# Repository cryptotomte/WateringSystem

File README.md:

# WateringSystem v2.3 (Hardware-Managed LDO Architecture)

## Overview
Cost-effective automated plant watering system with **2-domain optical isolation** for practical greenhouse automation. Features ESP32-based control, RS485 Modbus soil sensors, and simplified safety design optimized for enclosed environments.

**🔥 Latest Update v2.3**: Upgraded to TXS0108E bidirectional level shifter for faster RS485 communication - 1800x faster signal propagation while maintaining cost-effectiveness and reliability.

## Table of Contents
- [Features](#features)
- [Hardware Requirements](#hardware-requirements)
- [Software Dependencies](#software-dependencies)
- [Installation](#installation)
- [Usage](#usage)
- [Documentation](#documentation)
- [Testing](#testing)
- [Safety](#safety)
- [Contributing](#contributing)
- [License](#license)

## 🌟 Key Features

### Practical Safety & Isolation
- **Fast Level Shifting**: TXS0108E provides rapid voltage translation (110 Mbps)
- **2-Domain Architecture**: ESP32 (3.3V) → FIELD Domain (5V, level shifted)
- **Cost Effective**: Ultra-low cost design with high performance
- **Greenhouse Optimized**: Practical design for enclosed 12V environments

### Professional Monitoring
- **Multi-Parameter Soil Analysis**: NPK, pH, EC, moisture, temperature via RS485 Modbus
- **Environmental Sensing**: BME280 for ambient temperature, humidity, pressure
- **Real-time Monitoring**: Web interface with live sensor data
- **Remote Web Interface**: Responsive monitoring and configuration portal

### Smart Power Management
- **Hardware-Only Control**: LDO voltage converters provide always-on power management
- **Extended Runtime**: >48h operation on 20Ah LiFePO4 battery
- **Solar Ready**: MC4 connectors for future solar panel integration
- **Battery Monitoring**: Real-time voltage and capacity tracking
- **Simplified Design**: No software power control eliminates failure points
- **Instant Operation**: Always-on design eliminates startup delays

## 🔧 Hardware Architecture

### Hardware-Managed LDO System
```
12V LiFePO4 BATTERY ──┬── AMS1117-3.3 LDO ──► ESP32 Control Domain (Always-On)
                      │                      │ TXS0108E Level Shifter (3.3V↔5V)
                      │                      └── FIELD Domain (RS485 + Sensors)
                      │
                      └── AMS1117-5.0 LDO ──► Field Power Supply (Always-On)
                               │
                               └── Common Ground (GND_COMMON)
```

### Core Components
| Component | Model | Function | Domain |
|-----------|-------|----------|---------|
| Microcontroller | ESP32-WROOM-32E | Main processor + WiFi | 3.3V Always-On |
| RS485 Interface | **SP3485EN** | Modbus communication | 5V Always-On |
| Level Shifter | **TXS0108E** | 3.3V↔5V voltage translation | Signal Path |
| Power Regulation | **AMS1117** | LDO voltage regulators | Hardware Control |
| Environmental | BME280 | Temperature/humidity | 3.3V Control |
| Soil Sensor | RS485 Modbus | NPK/pH/EC/moisture | 5V Field |

### ⚡ Hardware-Managed Safety Features
**LDO-based design provides reliable, always-on operation:**
- **Fast Level Shifting**: TXS0108E (110 Mbps capability with 10ns propagation)
- **Hardware Control**: LDO regulators eliminate software power management
- **Common Ground**: Simplified design prevents ground loop issues
- **Always-On**: Eliminates startup delays and power sequencing complexity
- **Maintenance Free**: No complex power domain monitoring required

## Software Dependencies
- **Framework**: Arduino framework for ESP32
- **Build System**: PlatformIO
- **Libraries**:
  - Wire (for I2C communication)
  - Adafruit BME280 (for environmental sensor)
  - ModbusMaster (for RS485 soil sensor)
  - ESPAsyncWebServer (for web interface)
  - AsyncElegantOTA (for OTA updates)
  - LittleFS (for file storage)
  - ArduinoJson (for data processing)

## Installation
1. Clone the repository:
```bash
git clone https://github.com/cryptotomte/WateringSystem.git
cd WateringSystem
```

2. Install PlatformIO (if not already installed):
```bash
pip install platformio
```

### Windows PowerShell Commands
On Windows systems, PlatformIO may not be in PATH. Use these commands:

```powershell
# Build project
& "C:\Users\crypt\.platformio\penv\Scripts\pio.exe" run --environment wateringsystem

# Upload to device  
& "C:\Users\crypt\.platformio\penv\Scripts\pio.exe" run --target upload --environment wateringsystem
```

3. Build and upload the firmware:
```bash
platformio run --target upload
```

4. Upload the file system (for web interface):
```bash
platformio run --target uploadfs
```

## Usage
1. **Initial Setup**
   - Power on the device
   - Connect to the WiFi network "WateringSystem-XXXX"
   - Navigate to 192.168.4.1 in your web browser
   - Follow the setup wizard to configure your home WiFi network

2. **Web Interface**
   - Access the web interface by navigating to the IP address of the device
   - Monitor current environmental and soil conditions
   - Configure watering schedules and thresholds
   - View historical data and system logs

3. **OTA Updates**
   - Access the update page at http://[device-ip]/update
   - Upload new firmware files through the web interface

## Documentation
Detailed documentation is available in the `docs` directory:
- [System Requirements Specification](docs/requirements.md)
- [Architecture Documentation](docs/architecture.md)
- [Hardware Documentation](docs/hardware.md)
- [User Guide](docs/user-guide.md)
- [Testing Documentation](docs/testing.md)
- [Safety Documentation](docs/safety.md)
- [Release Notes](docs/release-notes.md)

## Testing
The system includes unit tests and integration tests that can be executed using PlatformIO:

```bash
# Run all tests
platformio test

# Run specific test
platformio test -e test_sensors
```

For complete testing documentation, see [Testing Documentation](docs/testing.md).

## Safety
The WateringSystem interfaces with both water and electricity. Important safety considerations:
- All electrical components must be properly isolated from water
- Use waterproof enclosure for outdoor installations
- Include proper grounding for lightning protection in outdoor installations
- Power supply must be isolated and conform to safety standards

For complete safety information, see [Safety Documentation](docs/safety.md).

## Contributing
Contributions to the WateringSystem project are welcome! Please read [CONTRIBUTING.md](CONTRIBUTING.md) for details on our code of conduct and the process for submitting pull requests.

## License
This project is licensed under the GNU Affero General Public License v3.0 or later (AGPL-3.0-or-later) - see the [LICENSE](LICENSE) file for details.

**Key License Points:**
- ✅ Commercial use allowed
- ✅ Private use allowed  
- ✅ Modification allowed
- ⚠️ **Must share source code** when distributing binaries
- ⚠️ **Must share source code** when running as network service (SaaS)
- ⚠️ **Must preserve copyright** and license notices
- ⚠️ All modifications must use the same license

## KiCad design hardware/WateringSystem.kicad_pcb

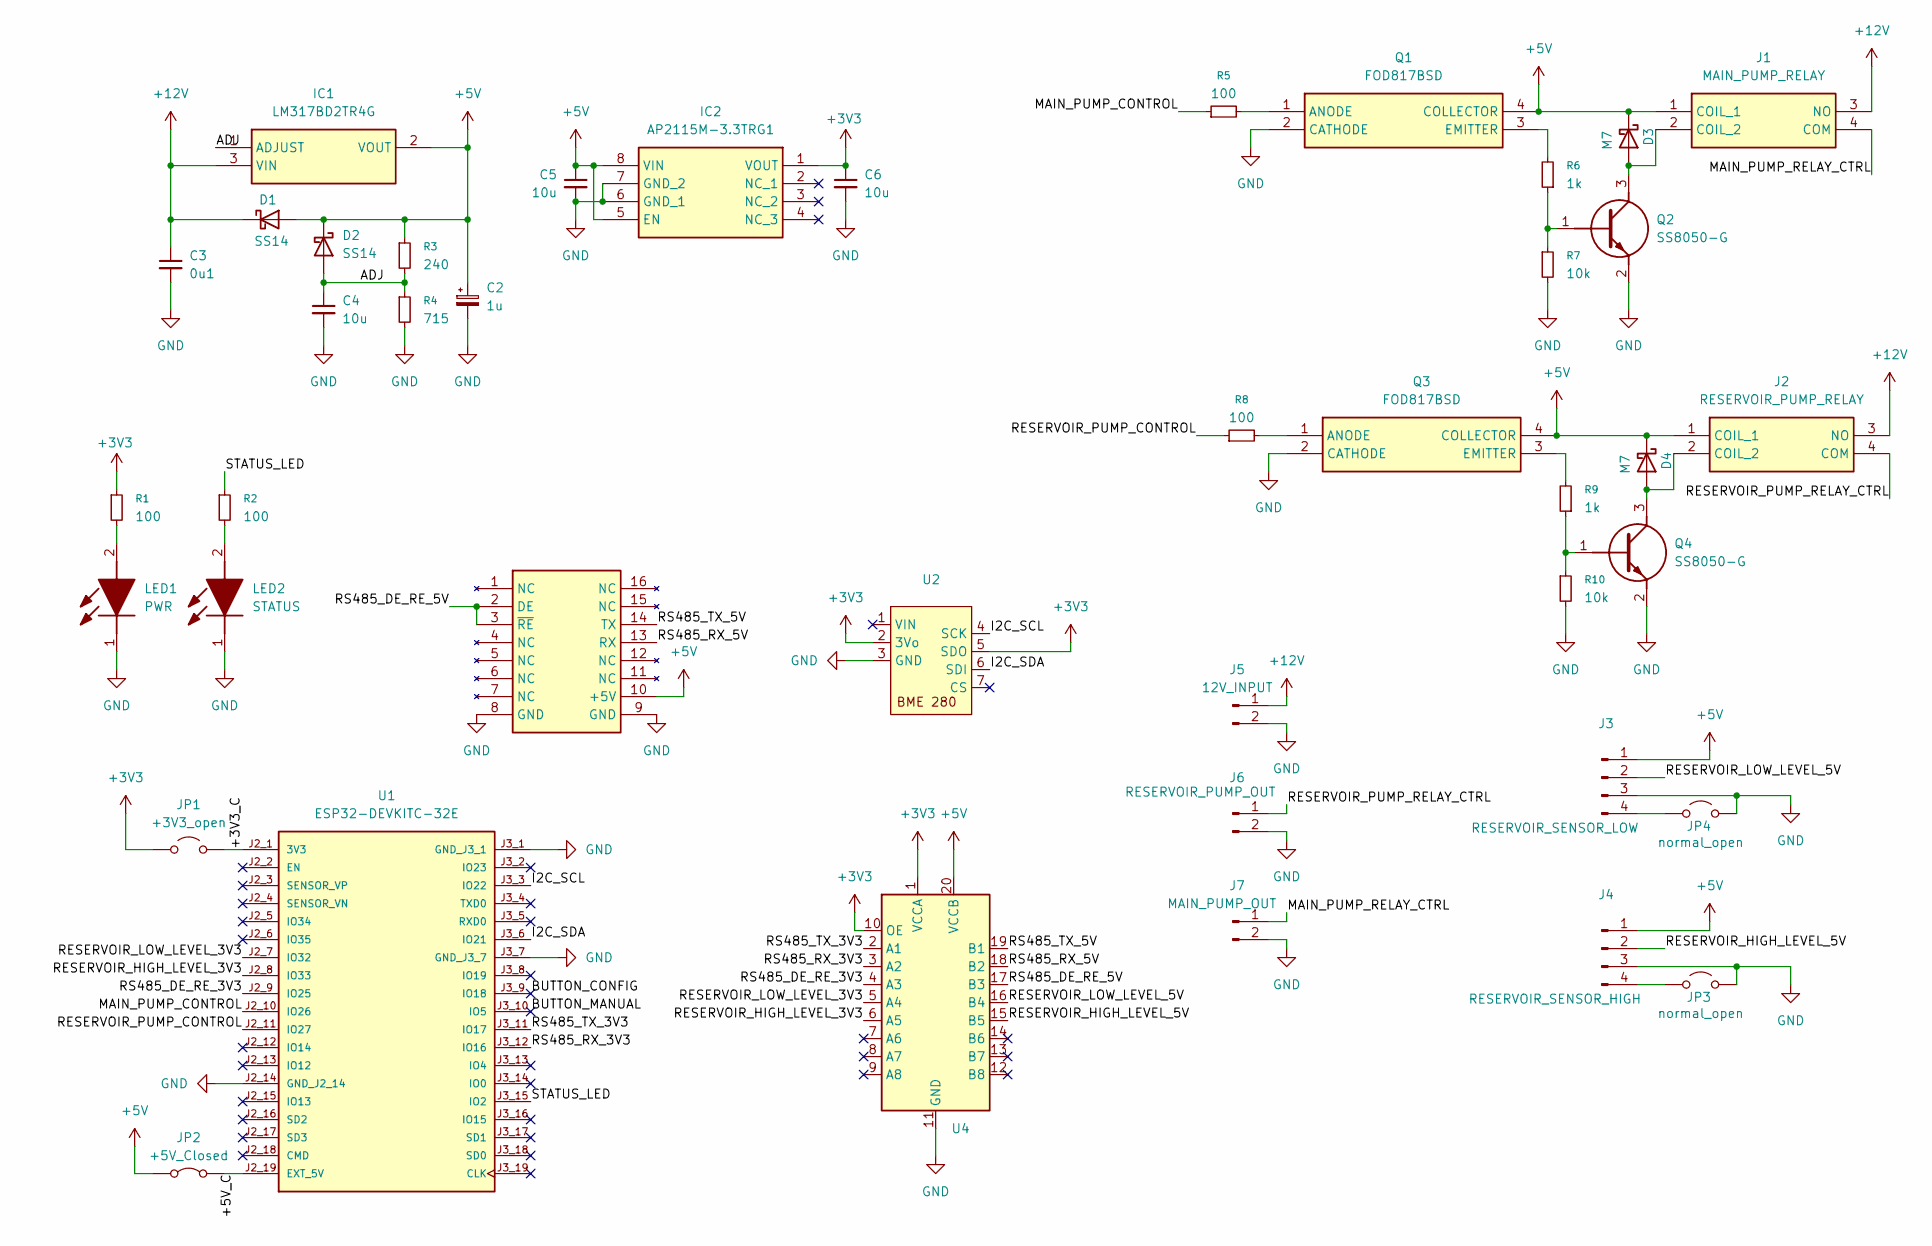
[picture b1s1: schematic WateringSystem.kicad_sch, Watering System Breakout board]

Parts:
Breakoutboard1: MAX485ESA+T_breakout
C2: 1u; CP_EIA-2012-12_Kemet-R
C3: 0u1; C_0805_2012Metric
C4, C5, C6: 10u; C_0805_2012Metric
D1, D2: SS14; D_SMA
D3, D4: M7; D_SMA
IC1: LM317BD2TR4G; Mouser Part Number 863-LM317BD2TR4G
IC2: AP2115M-3.3TRG1; SOIC127P600X175-8N; Mouser Part Number 621-AP2115M-3.3TRG1
J1: MAIN_PUMP_RELAY; 120715561; Mouser Part Number 655-1-2071556-1
J2: RESERVOIR_PUMP_RELAY; 120715561; Mouser Part Number 655-1-2071556-1
J3: RESERVOIR_SENSOR_LOW; JST_XH_B4B-XH-A_1x04_P2.50mm_Vertical
J4: RESERVOIR_SENSOR_HIGH; JST_XH_B4B-XH-A_1x04_P2.50mm_Vertical
J5: 12V_INPUT; WEID_1715010000
J6: RESERVOIR_PUMP_OUT; WEID_1715010000
J7: MAIN_PUMP_OUT; WEID_1715010000
JP1: +3V3_open; SolderJumper-2_P1.3mm_Open_RoundedPad1.0x1.5mm
JP2: +5V_Closed; SolderJumper-2_P1.3mm_Bridged_RoundedPad1.0x1.5mm
JP3, JP4: normal_open; SolderJumper-2_P1.3mm_Open_RoundedPad1.0x1.5mm
LED1: PWR; 150080SS75000; Mouser Part Number 710-150080SS75000
LED2: STATUS; LEDC2012X80N; Mouser Part Number 710-150080VS75000
Q1, Q3: FOD817BSD; SOP254P1016X385-4N; Mouser Part Number 512-FOD817BSD
Q2, Q4: SS8050-G; SOT95P240X115-3N; Mouser Part Number 750-SS8050-G
R1, R2, R5, R8: 100; R_0805_2012Metric
R3: 240; R_0805_2012Metric
R4: 715; R_0805_2012Metric
R6, R9: 1k; R_0805_2012Metric
R7, R10: 10k; R_0805_2012Metric
U1: ESP32-DEVKITC-32E; ESP32-DEVKITC-32E_MODULE_ESP32-DEVKITC-32E-for headers; PARTREV 1.4; DigiKey_Part_Number 1965-ESP32-DEVKITC-32E-ND
U2: BME_280_qt_version
U4: TXS10108E_breakout

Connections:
+3V3: C6.1, IC2.1 (VOUT), JP1.1 (A), R1.1, U2.2 (3Vo), U2.5 (SDO), U4.1 (VCCA), U4.10 (OE)
+5V: Breakoutboard1.10 (+5V), C2.1, C5.1, D1.2 (A), D2.1 (K), D3.1 (K), D4.1 (K), IC1.2 (VOUT), IC2.5 (EN), IC2.8 (VIN), J1.1 (COIL_1), J2.1 (COIL_1), J3.1, J4.1, JP2.1 (A), Q1.4 (COLLECTOR), Q3.4 (COLLECTOR), R3.1, U4.20 (VCCB)
+12V: C3.1, D1.1 (K), IC1.3 (VIN), J1.3 (NO), J2.3 (NO), J5.1
/+3V3_C: JP1.2 (B), U1.J2_1 (3V3)
/+5V_C: JP2.2 (B), U1.J2_19 (EXT_5V)
/ADJ: C4.1, D2.2 (A), IC1.1 (ADJUST), R3.2, R4.1
/BUTTON_CONFIG: U1.J3_9 (IO18)
/BUTTON_MANUAL: U1.J3_10 (IO5)
/I2C_SCL: U1.J3_3 (IO22), U2.4 (SCK)
/I2C_SDA: U1.J3_6 (IO21), U2.6 (SDI)
/MAIN_PUMP_CONTROL: R5.1, U1.J2_10 (IO26)
/MAIN_PUMP_RELAY_CTRL: J1.4 (COM), J7.1
/RESERVOIR_HIGH_LEVEL_3V3: U1.J2_8 (IO33), U4.6 (A5)
/RESERVOIR_HIGH_LEVEL_5V: J4.2, U4.15 (B5)
/RESERVOIR_LOW_LEVEL_3V3: U1.J2_7 (IO32), U4.5 (A4)
/RESERVOIR_LOW_LEVEL_5V: J3.2, U4.16 (B4)
/RESERVOIR_PUMP_CONTROL: R8.1, U1.J2_11 (IO27)
/RESERVOIR_PUMP_RELAY_CTRL: J2.4 (COM), J6.1
/RS485_DE_RE_3V3: U1.J2_9 (IO25), U4.4 (A3)
/RS485_DE_RE_5V: Breakoutboard1.2 (DE), Breakoutboard1.3 (~RE), U4.17 (B3)
/RS485_RX_3V3: U1.J3_12 (IO16), U4.3 (A2)
/RS485_RX_5V: Breakoutboard1.13 (RX), U4.18 (B2)
/RS485_TX_3V3: U1.J3_11 (IO17), U4.2 (A1)
/RS485_TX_5V: Breakoutboard1.14 (TX), U4.19 (B1)
/STATUS_LED: R2.1, U1.J3_15 (IO2)
GND: Breakoutboard1.8 (GND), Breakoutboard1.9 (GND), C2.2, C3.2, C4.2, C5.2, C6.2, IC2.6 (GND_1), IC2.7 (GND_2), J3.3, J4.3, J5.2, J6.2, J7.2, JP3.2 (B), JP4.2 (B), LED1.1 (K), LED2.1 (K), Q1.2 (CATHODE), Q2.2 (E), Q3.2 (CATHODE), Q4.2 (E), R4.2, R7.2, R10.2, U1.J2_14 (GND_J2_14), U1.J3_1 (GND_J3_1), U1.J3_7 (GND_J3_7), U2.3 (GND), U4.11 (GND)
unnamed: D3.2 (A), J1.2 (COIL_2), Q2.3 (C)
unnamed: D4.2 (A), J2.2 (COIL_2), Q4.3 (C)
unnamed: J3.4, JP4.1 (A)
unnamed: J4.4, JP3.1 (A)
unnamed: LED1.2 (A), R1.2
unnamed: LED2.2 (A), R2.2
unnamed: Q1.1 (ANODE), R5.2
unnamed: Q1.3 (EMITTER), R6.2
unnamed: Q2.1 (B), R6.1, R7.1
unnamed: Q3.1 (ANODE), R8.2
unnamed: Q3.3 (EMITTER), R9.2
unnamed: Q4.1 (B), R9.1, R10.1

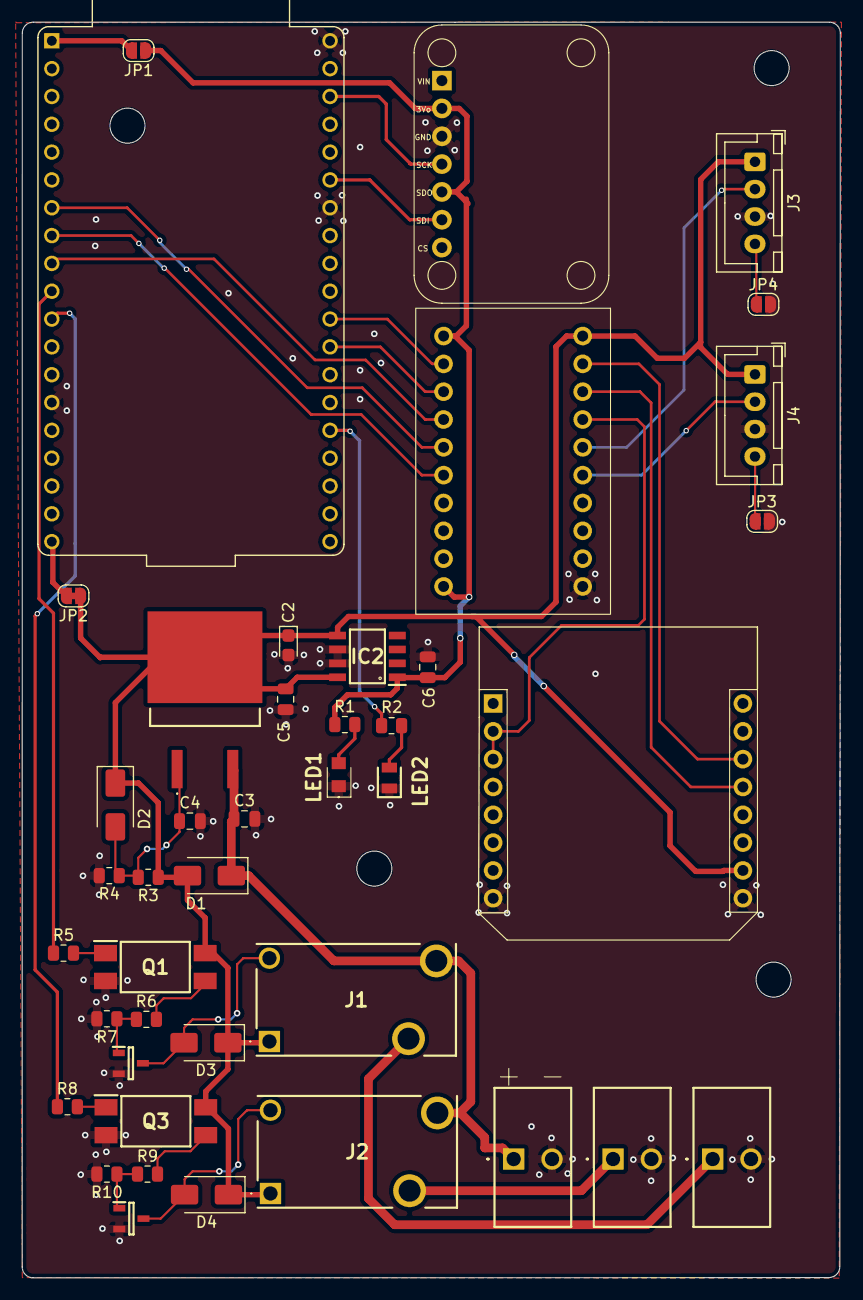
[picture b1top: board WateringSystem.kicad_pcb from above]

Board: 4 copper layers, 74.7 x 114.6 mm, 42 parts (0 on the bottom side), 36 nets.

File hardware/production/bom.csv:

Designator,Footprint,Quantity,Value,LCSC Part #
BREAKOUTBOARD1,MAX485ESA+T_breakout,1,~,
C2,CP_EIA-2012-12_Kemet-R,1,1u,
C3,0805,1,0u1,
"C4, C5, C6",0805,3,10u,
"D1, D2",D_SMA,2,SS14,
"D3, D4",D_SMA,2,M7,
IC1,LM317BD2TR4G,1,LM317BD2TR4G,
IC2,SOIC127P600X175-8N,1,AP2115M-3.3TRG1,
J1,120715561,1,MAIN_PUMP_RELAY,
J2,120715561,1,RESERVOIR_PUMP_RELAY,
J3,JST_XH_B4B-XH-A_1x04_P2.50mm_Vertical,1,RESERVOIR_SENSOR_LOW,
J4,JST_XH_B4B-XH-A_1x04_P2.50mm_Vertical,1,RESERVOIR_SENSOR_HIGH,
J5,WEID_1715010000,1,12V_INPUT,
J6,WEID_1715010000,1,RESERVOIR_PUMP_OUT,
J7,WEID_1715010000,1,MAIN_PUMP_OUT,
JP1,SolderJumper-2_P1.3mm_Open_RoundedPad1.0x1.5mm,1,+3V3_open,
JP2,SolderJumper-2_P1.3mm_Bridged_RoundedPad1.0x1.5mm,1,+5V_Closed,
"JP3, JP4",SolderJumper-2_P1.3mm_Open_RoundedPad1.0x1.5mm,2,normal_open,
LED1,150080SS75000,1,PWR,
LED2,LEDC2012X80N,1,STATUS,
"Q1, Q3",SOP254P1016X385-4N,2,FOD817BSD,
"Q2, Q4",SOT95P240X115-3N,2,SS8050-G,
"R1, R2, R5, R8",0805,4,100,
"R10, R7",0805,2,10k,
R3,0805,1,240,
R4,0805,1,715,
"R6, R9",0805,2,1k,
U1,ESP32-DEVKITC-32E_MODULE_ESP32-DEVKITC-32E-for headers,1,ESP32-DEVKITC-32E,
U2,BME_280_qt_version,1,~,
U4,TXS10108E_breakout,1,~,

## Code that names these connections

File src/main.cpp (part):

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#include "hardware/RS485Config.h" // Hardware configuration for RS485

// Pin definitions based on hardware.md specification with TXS0108E level shifter
#define PIN_I2C_SDA           21
#define PIN_I2C_SCL           22
#define PIN_RS485_TX          16  // ESP32 TX -> TXS0108E A2 -> B2 -> Click pin13 (DI)
#define PIN_RS485_RX          17  // ESP32 RX <- TXS0108E A1 <- B1 <- Click pin14 (RO)
#define PIN_RS485_DE          25  // Direction control via TXS0108E A3
#define PIN_MAIN_PUMP_CONTROL 26  // Main Water Pump MOSFET Gate (unchanged)
#define PIN_RESERVOIR_PUMP_CONTROL 27  // Reservoir Filling Pump MOSFET Gate (unchanged)
#define PIN_RESERVOIR_LOW_LEVEL   32  // Sensor for low water level in reservoir (unchanged)
#define PIN_RESERVOIR_HIGH_LEVEL  33  // Sensor for high water level in reservoir (unchanged)
#define PIN_STATUS_LED        2       
#define PIN_BUTTON_MANUAL     5       
#define PIN_BUTTON_CONFIG     18

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HardwareSerial rs485Serial(2);  // Using UART2 for RS485
SP3485ModbusClient modbusClient(&rs485Serial, PIN_RS485_DE); // Using TXS0108E level shifter - hardware managed
ModbusSoilSensor soilSensor(&modbusClient, SOIL_SENSOR_MODBUS_ADDR, "SoilSensor");
WaterPump plantPump(PIN_MAIN_PUMP_CONTROL, "PlantPump");         // Renamed for clarity
WaterPump reservoirPump(PIN_RESERVOIR_PUMP_CONTROL, "ReservoirPump"); // Added new pump for filling reservoir
LittleFSStorage dataStorage;
WateringController controller(&envSensor, &soilSensor, &plantPump, &dataStorage);
WateringSystemWebServer webServer(&controller, &envSensor, &soilSensor, &plantPump, &dataStorage, WEB_SERVER_PORT, &reservoirPump);
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    while (WiFi.status() != WL_CONNECTED && 
           millis() - startAttemptTime < WIFI_TIMEOUT) {
        Serial.print(".");
        digitalWrite(PIN_STATUS_LED, !digitalRead(PIN_STATUS_LED));  // Toggle LED
        delay(500);
    }
    
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  Serial.println("Architecture: LDO-powered domains with TXS0108E level shifting");
  
  // Initialize status LED
  pinMode(PIN_STATUS_LED, OUTPUT);
  digitalWrite(PIN_STATUS_LED, HIGH);  // Turn on while initializing
  
  // Initialize buttons with pull-ups
  pinMode(PIN_BUTTON_MANUAL, INPUT_PULLUP);
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  pinMode(PIN_RESERVOIR_LOW_LEVEL, INPUT_PULLUP);
  pinMode(PIN_RESERVOIR_HIGH_LEVEL, INPUT_PULLUP);
    // Initialize I2C for BME280 (ESP32 domain)
  Wire.begin(PIN_I2C_SDA, PIN_I2C_SCL);
  Serial.println("I2C initialized for BME280");
    // Initialize RS485 UART with TXS0108E level shifter
  rs485Serial.begin(9600, SERIAL_8N1, PIN_RS485_RX, PIN_RS485_TX);
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  systemReady = true;
  
  // Turn off status LED once system is ready
  digitalWrite(PIN_STATUS_LED, LOW);
  
  Serial.println("System initialization complete");
  Serial.println("--------------------------------------------");
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  // LED status indication
  if (apMode) {
    // Fast blinking in AP mode
    digitalWrite(PIN_STATUS_LED, ((millis() / 200) % 2) ? HIGH : LOW);
  } else if (plantPump.isRunning()) {
    // Medium blinking when pump is running
    digitalWrite(PIN_STATUS_LED, ((millis() / 500) % 2) ? HIGH : LOW);
  } else {
    // Just a short blink every 3 seconds to show system is running
    digitalWrite(PIN_STATUS_LED, ((millis() % 3000) < 100) ? HIGH : LOW);  }
    // Monitor and maintain WiFi connection
  monitorWiFiConnection();
  
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    while (digitalRead(PIN_BUTTON_CONFIG) == LOW && configButtonHoldTime < 50) {
        delay(100);
        configButtonHoldTime++;
        digitalWrite(PIN_STATUS_LED, configButtonHoldTime % 2);  // Blink LED
    }
    
    if (configButtonHoldTime >= 50) {  // Button held for 5+ seconds
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
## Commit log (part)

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2025-04-15 Inital project setup
2025-04-15 Add AsyncElegantOTA support and web interface files
2025-04-15 Update README.md with comprehensive project description and features
2025-04-15 Uppdaterat författarnamn i alla header- och implementationsfiler
2025-04-15 Add update method to IWaterPump interface
2025-04-15 Rename WebServer to WateringSystemWebServer to avoid conflicts
    - Renamed class and files to WateringSystemWebServer to avoid name conflicts with ESP32's built-in WebServer
    - Created new header and implementation files with the new name
    - Updated main.cpp to use the new header file
    - Maintained the same functionality without behavioral changes
    - Removed old WebServer files
2025-04-15 Update header files with consistent include guards and formatting
    - Update all header files with consistent include guards
    - Fix formatting and comments in header files
    - Add wifi_setup.html for AP mode configuration
    - Update platformio.ini build settings
2025-04-16 Add reservoir pump control and improve system management
    - Add reservoir pump on pin 27 for filling the water reservoir
    - Move status LED to pin 2 (was previously on pin 27)
    - Rename waterPump to plantPump for better clarity
    - Update pin definitions for improved readability
    - Add WebServer implementation files
    - Update documentation in user-guide
2025-04-16 Add reservoir pump functionality with auto-fill feature
    - Add new hardware support for reservoir pump and water level sensors
    - Implement reservoir control logic in main.cpp
    - Update web interface with reservoir management controls
    - Update documentation with reservoir pump specifications
    - Fix getReservoirStatus function to return bool according to callback type
    - Fix method name in ModbusSoilSensor from writeHoldingRegister to writeSingleRegister
2025-04-16 Fix auto watering toggle functionality in web interface
    - Implement AsyncCallbackJsonWebHandler for proper JSON parsing
    - Separate handlers for JSON and form-based requests
    - Improve debug logging for better troubleshooting
    - Update header file with new method declarations
    The web interface can now correctly enable/disable auto watering through
    the JSON API endpoints.
2025-04-17 fix: Remove empty :root rule in styles.css
2025-04-17 refactor: update main.cpp and remove deprecated WebServer.cpp
2025-05-05 Fix LittleFS file path handling and config file management
    - Update LittleFSStorage to properly handle file paths with leading slashes
    - Add automatic creation of config.json file when missing
    - Improve error handling and logging for file operations
    - Fix endpoint path handling in WateringSystemWebServer class
    - Update LittleFSStorage constructor to handle String objects correctly
    - Add detailed logging for debugging file path issues
2025-05-05 fix: use form data instead of JSON for watering requests
    - Change startWatering function to use form data format
    - Remove problematic raw body handler in WateringSystemWebServer
    - Add favicon references to HTML files
    - Fix memory leak issues with AsyncWebServer JSON handling
    The ESP32's AsyncWebServer library has issues with JSON data on
    /control/water/start endpoint, causing memory leaks and device crashes
2025-05-05 add: include favicon and update header files
    - Add favicon.ico for web interface
    - Update WateringSystemWebServer.h with proper function declarations
    - Improve debug logging in WaterPump.cpp for better troubleshooting
    - Complete the fix for the JSON handling issue
2025-05-06 chore: remove launch.json exception from .gitignore
    - Exclude VS Code launch.json from version control
    - Add comment explaining why launch.json should be ignored
    - This prevents user-specific configurations from being committed
2025-05-28 feat: Implement dark theme and improve reservoir control layout
2025-06-03 style: update wifi_setup.html to match modern Tailwind CSS design
2025-06-09 Simplify architecture to cost-effective 2-domain system
    - Replace complex 3-domain isolation with practical 2-domain optical isolation
    - Remove expensive MIKROE-4156 and TMR 1-1215 components
    - Update BOM cost from ~6000 SEK to 3108 SEK (50% reduction)
    - Clean up 18 duplicate/outdated documentation files
    - Update all documentation for simplified FOD817BSD-only isolation
    - Maintain 5kV optical isolation adequate for greenhouse environments
2025-06-09 Add documentation cleanup completion report - Comprehensive summary of architecture simplification - Cost analysis showing 50% BOM reduction - Technical validation of 2-domain optical isolation - Com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
2025-06-09 Update gitignore to exclude local PlatformIO documentation
2025-06-09 Remove auto-generated documentation files and enhance WiFi stability
    - Remove outdated documentation files that were auto-restored by VS Code
    - Keep only essential docs: requirements.md, architecture.md, hardware.md
    - Enhanced WiFi stability with monitoring, diagnostics, and auto-reconnection
    - Added software watchdog and emergency WiFi reset functionality
    - Improved web interface connection status handling
2025-06-09 Update gitignore to prevent auto-generated files
2025-06-09 Add documentation backup file explaining auto-restore issue
2025-06-10 Fix critical sensor failure and implement emergency safety measures
    - Add brownout detector disable to prevent WiFi-related resets
    - Implement comprehensive fail-safe mechanisms for sensor timeouts
    - Add timestamp-based sensor validation with 30-second timeout
    - Emergency pump stop when sensor data unavailable
    - Enhanced debug infrastructure for sensor initialization
    - Improve RS485 communication timing and error handling
2025-06-11 Upgrade from FOD817 optocouplers to TXS0108E level shifter
    - Replace FOD817BSD optical isolation with TXS0108E bidirectional level shifter
    - Achieve 1800x faster signal propagation (10ns vs 18µs)
    - Support up to 110 Mbps data rate vs ~1 Mbps limitation
    - Reduce component count from 3 optocouplers to 1 level shifter IC
    - Update timing constants for faster DE/RE switching (10µs vs 200µs)
    - Modify GPIO pin assignments for TXS0108E Output Enable (GPIO 26)
2025-06-11 Remove temporary documentation and improve web UI responsiveness
    - Remove KORREKT_KOMPONENTBYTE.md (changes documented in commit history)
    - Update web UI refresh rate: system status now updates every 5 seconds
    - Water level indicator and pump status now respond much faster
    - Improves user experience for reservoir pump monitoring
    Performance improvements:
    - Water level updates: 15s 5s (3x faster)
2025-06-16 Add initial KiCad 9 project files for PCB design
    - Add WateringSystem.kicad_pro: Project configuration file
    - Add WateringSystem.kicad_sch: Empty schematic ready for component placement
    - Add WateringSystem.kicad_pcb: Empty PCB layout ready for routing
    - Add sym-lib-table: Symbol library configuration table
    Project structure now ready for:
    - ESP32 and sensor component placement
2025-06-25 Fix gitignore pattern for KiCad autosave files
    - Add ~_autosave* pattern to properly ignore files starting with tilde
    - Ensures lock files like ~_autosave-*.kicad_pcb.lck are properly ignored
2025-07-05 Fix manual watering mode and remove soil sensor debug logging
    - Add manual mode support to WaterPump with isManualMode() and setManualMode()
    - Modify safety functions to only apply to automatic watering mode
    - Manual watering now bypasses sensor-based safety checks
    - Remove excessive DEBUG-INIT logging from soil sensor initialization
    - Fix timing display bug in pump debug messages
    - Add comprehensive debug logging for pump operations with mode tracking
2025-07-24 Fix RS485 communication and update documentation
    Major improvements to RS485 Modbus soil sensor communication:
    Hardware fixes:
    - Fix GPIO pin configuration: TX=GPIO17, RX=GPIO16 (was swapped)
    - Optimize TXS0108E timing delays from 10µs to 50µs for reliable switching
    - Update RS485Config.h with verified timing constants
    Software improvements:
2025-07-29 Add rs485test diagnostic command and fix soil sensor communication
    - Implement rs485test/test commands in handleSerialCommands()
    - Add isolated RS485 client testing functionality
    - Parse and display raw register values with detailed output
    - Enable runtime diagnostics for soil sensor troubleshooting
    - Successfully resolved Error 3 communication issues
    - Production system now fully functional with soil sensor readings
2025-08-22 Change license from MIT to AGPL-3.0-or-later
    - Replace LICENSE with full AGPL-3.0-or-later text
    - Add SPDX headers to all source files (.cpp, .h)
    - Update CONTRIBUTING.md with DCO and copyleft requirements
    - Preserve attribution and require source sharing for modifications
    - Ensure commercial use allowed but changes must be returned
2025-08-22 Update README.md license references from MIT to AGPL-3.0-or-later
    - Change license badge from MIT to AGPL-3.0-or-later
    - Update License section with detailed AGPL-3.0-or-later explanation
    - Add key license points highlighting copyleft requirements
    - Clarify source code sharing obligations for distribution and SaaS
2026-04-12 Lägg till feature-ideas.md med multi-zon och produktions-PCB koncept
2026-06-09 hardware: commit April design work — schematic pin fixes, PCB layout session, rev2 BOM (THVD1426), JLCPCB production files
2026-06-09 added needed changes to these files
2026-06-09 chore: initialize spec-kit
2026-06-11 docs(spec): PR-06 nvs-littlefs-storage spec, plan, tasks and design artifacts
    - Feature spec with 2026-06-11 clarifications (>=30-day retention,
    settable interval items, reservoir flags deferred to PR-05)
    - Plan with verified research D1-D10 (littlefs image build, NVS on
    linux target, atomicity model), data model, contracts, quickstart
    - 36 tasks across 8 phases; cross-artifact analysis findings fixed
    (FR-013 Locked* decorators, 10-metric budget cap, linux-target
2026-06-12 feat(interfaces): IDataStorage contract header
    Sensor history, rotating event log and storage statistics interface
    per contracts/IDataStorage.md. Contract-level bounds (kMaxMetrics,
    kEventDetailMaxLen, event categories) live here as the single source
    of truth for implementations, mocks and tests.
    Task: T015
    Spec: 003-nvs-littlefs-storage
2026-06-12 feat(storage): LittleFsDataStorage declaration and stub
    POSIX-stdio data storage skeleton with injectable base path and
    stats provider (no esp_littlefs/IDF includes, builds on the linux
    preview target). History methods stubbed for T021, event methods
    for T024. Registered in the storage component for both targets.
    Task: T017
    Spec: 003-nvs-littlefs-storage
2026-06-12 test(storage): range-query and mock-conformance suites
    Inclusive chronological range queries, empty-result semantics
    (no data / unknown metric / t0>t1, FR-009), unsafe-metric-name
    rejection, and MockDataStorage held to the same contract (FR-012).
    Per-test POSIX temp dirs with RAII cleanup; written against the
    T017 stub, red until T021.
    Task: T018
2026-06-12 test(storage): torn-tail handling suites
    A partial trailing record (size % 8 != 0, simulated power loss) is
    logically truncated on read with earlier records intact, and the
    next append repairs the tail so the chunk stays 8-byte aligned
    (research D5, contract invariant 2).
    Task: T020
    Spec: 003-nvs-littlefs-storage
2026-06-12 feat(storage): implement LittleFsDataStorage sensor history
    History per data-model.md: /hist/<metric>/<first_epoch>.dat chunks
    of 8-byte little-endian records, sealed at 8 KiB, ring-evicted at
    10 chunks per metric, 10-distinct-metric budget guard. Durability
    via fflush+fsync per append; torn tails logically truncated on read
    and repaired (truncate to valid prefix) before the next append.
    Active chunk is derived from the files, so restarts need no
2026-06-13 docs(spec): T025 verified — full host suite green on linux target (44 tests, 0 failures)
    Spec: 003-nvs-littlefs-storage

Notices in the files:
src/main.cpp:
SPDX-FileCopyrightText: 2025 Cryptotomte
SPDX-License-Identifier: AGPL-3.0-or-later
README.md:
License: AGPL-3.0-or-later
